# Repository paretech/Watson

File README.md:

Watson
======

Watson is a relatively simple RF power meter based on the "120 dB Measurement System" outlined in the Analog Devices (AD) AD8307 data sheet. Watson has a narrow and fixed measurement band centered on 10.7 MHz and was developed as the detector for a low cost spectrum analyzer design.

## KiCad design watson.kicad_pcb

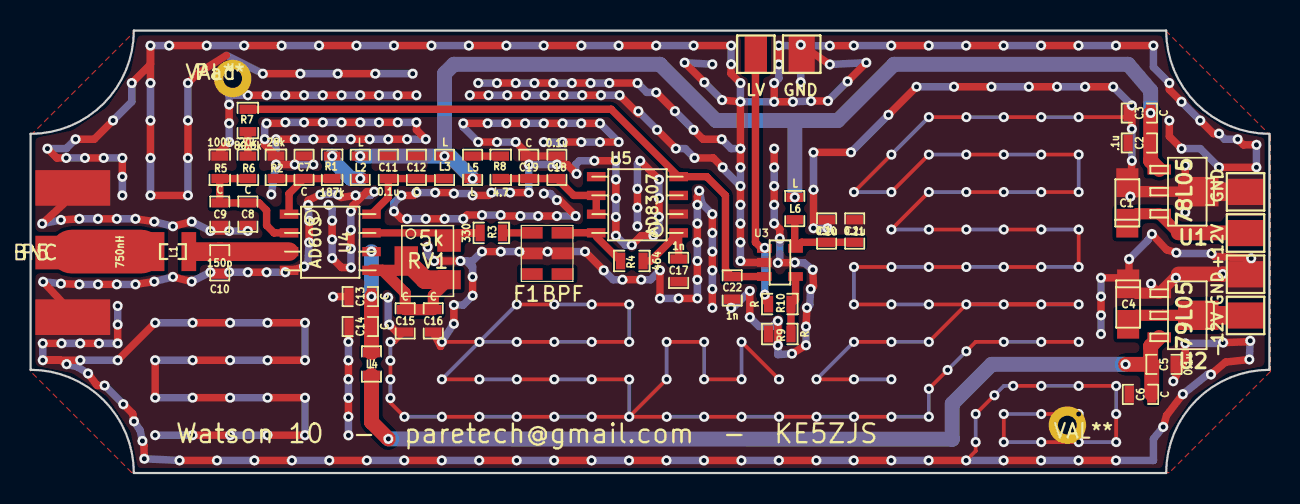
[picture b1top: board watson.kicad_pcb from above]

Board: 2 copper layers, 84.0 x 30.0 mm, 54 parts (0 on the bottom side), 24 nets.

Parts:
+12V: CONN_1; PIN_ARRAY_1
-12V: CONN_1; PIN_ARRAY_1
C1, C4: 33u; c_tant_A
C2: .1u; SM0603_Capa
C3, C6, C7, C8, C9, C12, C13, C14, C15, C16, C19: C; SM0603_Capa
C5, C11, C18, C20, C21: 0.1u; SM0603_Capa
C10: 150p; SM0603_Capa
C17, C22: 1n; SM0603_Capa
F1: BPF; SFEC
GND: CONN_1; PIN_ARRAY_1
GND#2: CONN_1; PIN_ARRAY_1
GND#3: Val**; PIN_ARRAY_1
L1: 750nH; 180mm_ChipCoil
L2, L3, L4, L5, L6: L; SM0603_Inductor
LV: CONN_1; PIN_ARRAY_1
P5: BNC; sma-edge-062
Pad: VAL**; Pad
R1: 187k; SM0603_Resistor
R2: 28k; SM0603_Resistor
R3: 330; SM0603_Resistor
R4: 464; SM0603_Resistor
R5: 100k; SM0603_Resistor
R6: 20k; SM0603_Resistor
R7: 80.6k; SM0603_Resistor
R8: 4.7; SM0603_Resistor
R9, R10: R; SM0603_Resistor
RV1: 5k; VRSM3932_JHOOK
U1: 78L05; sot89
U2: 79L05; sot89
U3: AD8031; sot23
U4: AD603; so-8
U5: AD8307
hole: VAL**; hole

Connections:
+5V: C2.2, C3.1, L2.1, L3.1, L5.1, L6.1, U1.1
-5V: C5.2, C6.1, L4.1, U2.3
/+Vs: C20.1, C21.1, L6.2, U3.5
/GPOS: C7.1, R1.1, R2.2, U4.1
/V+: +12V.1, C1.1, U1.3
/V-: -12V.1, C4.1, U2.2
/VNEG: C13.1, C14.1, L4.2, U4.6
/VPOS: C11.1, C12.1, L3.2, U4.8
/VPS: C18.2, C19.2, R8.1, U5.6, U5.7
GND: C1.2, C2.1, C3.2, C4.1, C5.1, C6.2, C7.2, C8.2, C9.2, C10.2, C11.2, C12.2, C13.2, C14.2, C15.2, C16.2, C17.2, C18.1, C19.1, C20.2, C21.2, C22.2, F1.2, F1.5, GND.1, GND#2.1, GND#3.1, P5.2, Pad.1, R2.1, R5.1, R9.2, U1.2, U2.1, U3.2, U4.4, U5.2, hole.1
unnamed: R6.1, R7.1
unnamed: C17.1, R4.1, U5.1
unnamed: F1.6, R4.2, U5.8
unnamed: C8.1, C9.1, R5.2, R6.2, U4.2
unnamed: F1.1, R3.2
unnamed: R3.1, RV1.3, U4.7
unnamed: C15.1, C16.1, RV1.1, RV1.2, U4.5
unnamed: L1.1, P5.1
unnamed: LV.1, R10.1, U3.1
unnamed: R9.1, R10.2, U3.4
unnamed: C22.1, R7.2, U3.3, U5.4
unnamed: L2.2, R1.2
unnamed: L5.2, R8.2
unnamed: C10.1, L1.2, U4.3

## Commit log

2013-09-21 Schematic, schematic library, partial footprint.
2013-09-21 Renumbered components in schematic and added capacitors to module file.
2013-09-22 Updated module library to include foot prints for edge mount SMA, 0603 resistor and 0603 capacitor.
2013-09-22 Schematic reworked.
2013-09-24 Added ferrite bead module and created an autoplace PCB.
2013-09-25 Added footprints SOT89, c_tant_A, AD8307; Added new footprint parts to pcb.
2013-09-26 Added chip coil layout
2013-09-30 Added AD8031 to buffer output of AD8307.
2013-10-01 add image of Watson's schematic
2013-10-01 Added cover image for Watson's board layout
2013-10-01 Update README.md
    Added some pictures to readme.
2013-12-10 This is the initial manufactured version of Watson, Watson 10 to be exact.
2013-12-10 Added CSV Bom
2014-04-02 I'm a terrible committer. I think these are the latest files that I actually sent to OSH Park... I hope....
2014-04-05 Deleted grid_origin (line 68) for Arch Linux backwards compatibility with stable community release 2013-05-18 BZR4017
2014-04-06 Added first data set, MATLAB Script to plot graph and PNG of resulting graph.
2014-04-08 Added support for basic log conformance plot at 10.7 MHz
2014-04-11 Added updated measurement data, scripts to generate plots and generated plots. Removed pdf schematic because it was outdated.
2014-04-15 Reorganized repo and added a few images and pdf schematic.
2014-04-16 Update README.md
    Updated README.md with latest screen caps and preliminary performance data.
2014-04-19 Added 4 new images of populated and unpopulated PCB in 2 different sizes each
2014-04-19 Added photos to readme
2014-04-23 Updated MATLAB plot scripts to reflect new directory structure. Fixed difference equation in Log Conformance graph to match graphs in AD8307 datasheets
2014-04-23 Fixed log_response script paths
2014-04-25 Added new CSV file containing 9 frequency sweeps. First row and column of csv file contains the frequency and power information. Updated existing graph scripts to use new file. No new graphs added ye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
2014-04-25 Updated README to remove duplicate image
2014-04-27 Consolidated graph scripts to single MATLAB m file. Changed graph file names. Added log response graph over various frequencies. Updated README.md to reflect graph changes.
